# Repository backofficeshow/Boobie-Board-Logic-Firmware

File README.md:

# Boobie-Board-Logic-Firmware
Firmware For The Boobie Board Logic Analyser

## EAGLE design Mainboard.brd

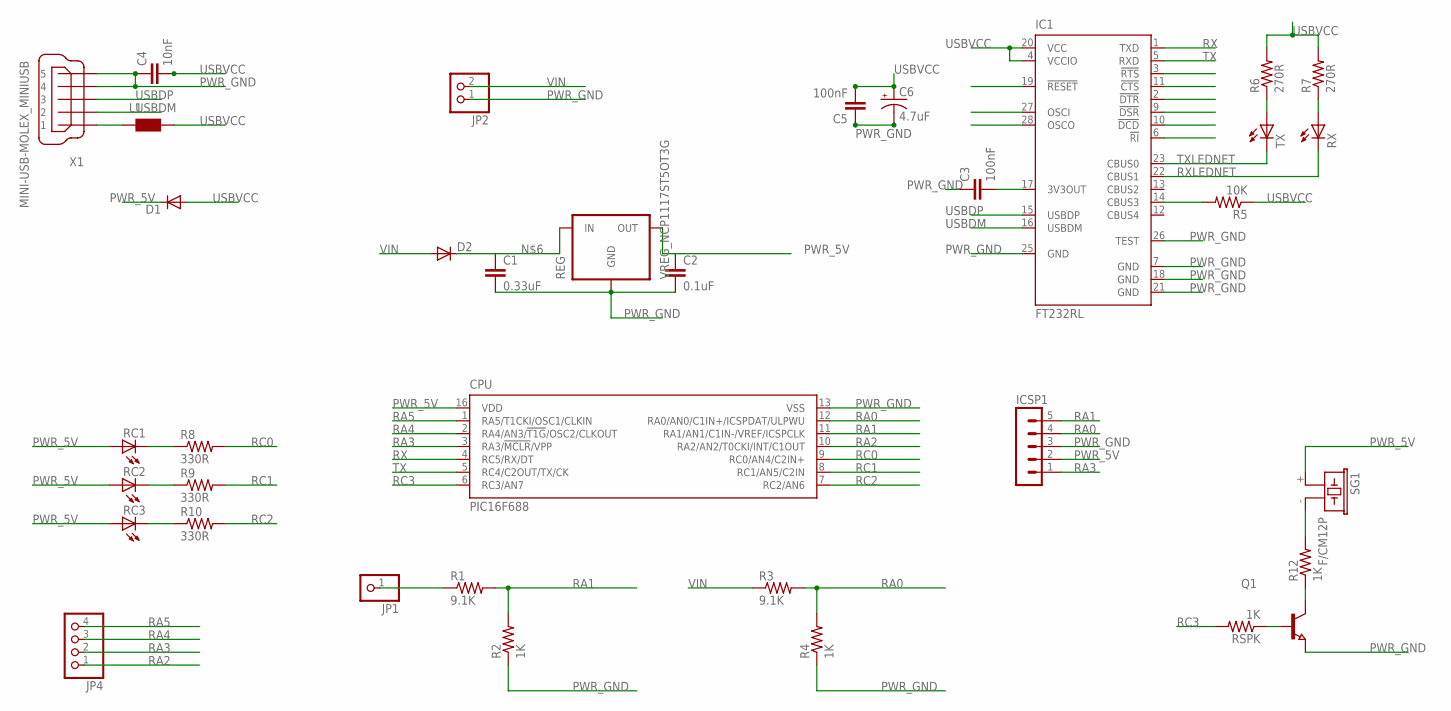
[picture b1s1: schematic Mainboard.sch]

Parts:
C1: 0.33uF; 0805
C2: 0.1uF; 0805
C3, C5: 100nF; 0805
C4: 10nF; 0805
C6: 4.7uF; EIA3528
CPU: PIC16F688; QFN16-4X4
D1, D2: DIODESMA; SMA-DIODE
IC1: FT232RL; SSOP28
ICSP1: MA05-1
JP1: PINHD-1X1; 1X01
JP2: PINHD-1X2; 1X02
JP4: PINHD-1X4; 1X04
L1: WE-CBF_0805; 0805
Q1: NPN-TRANSISTOR_SOT23; SOT23
R1, R3: 9.1K; 0805
R2, R4, R12: 1K; 0805
R5: 10K; 0805
R6, R7: 270R; 0805
R8, R9, R10: 330R; 0805
RC1, RC2, RC3: LED0603; LED-0603
REG: VREG_NCP1117ST5OT3G; SOT233
RSPK: 1K; 0805
RX: LED0603; LED-0603
SG1: F/CM12P
TX: LED0603; LED-0603
X1: MINI-USB-MOLEX_MINIUSB; 32005-201

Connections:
unnamed: R8.1, RC1.C
unnamed: JP1.1, R1.1
unnamed: R9.1, RC2.C
unnamed: R10.1, RC3.C
unnamed: R7.1, RX.A
unnamed: C1.1, D2.C, REG.3 (IN)
unnamed: C3.2, IC1.17 (3V3OUT)
unnamed: Q1.3 (C), R12.1
unnamed: Q1.1 (B), RSPK.1
unnamed: IC1.14 (CBUS3), R5.2
unnamed: L1.1, X1.1
unnamed: R12.2, SG1.- (2)
PWR_5V: C2.1, CPU.16 (VDD), D1.C, ICSP1.2, RC1.A, RC2.A, RC3.A, REG.2 (OUT), SG1.+ (1)
PWR_GND: C1.2, C2.2, C3.1, C4.1, C5.1, C6.C (-), CPU.13 (VSS), IC1.7 (GND), IC1.18 (GND), IC1.21 (GND), IC1.25 (GND), IC1.26 (TEST), ICSP1.3, JP2.1, Q1.2 (E), R2.1, R4.1, REG.1 (GND), X1.4, X1.5
RA0: CPU.12 (RA0/AN0/C1IN+/ICSPDAT/ULPWU), ICSP1.4, R3.2, R4.2
RA1: CPU.11 (RA1/AN1/C1IN-/VREF/ICSPCLK), ICSP1.5, R1.2, R2.2
RA2: CPU.10 (RA2/AN2/T0CKI/INT/C1OUT), JP4.1
RA3: CPU.3 (RA3/!MCLR!/VPP), ICSP1.1, JP4.2
RA4: CPU.2 (RA4/AN3/!T1G!/OSC2/CLKOUT), JP4.3
RA5: CPU.1 (RA5/T1CKI/OSC1/CLKIN), JP4.4
RC0: CPU.9 (RC0/AN4/C2IN+), R8.2
RC1: CPU.8 (RC1/AN5/C2IN), R9.2
RC2: CPU.7 (RC2/AN6), R10.2
RC3: CPU.6 (RC3/AN7), RSPK.2
RX: CPU.4 (RC5/RX/DT), IC1.1 (TXD)
RXLEDNET: IC1.22 (CBUS1), RX.C
TX: CPU.5 (RC4/C2OUT/TX/CK), IC1.5 (RXD)
TXLEDNET: IC1.23 (CBUS0), TX.C
TXNET: R6.1, TX.A
USBDM: IC1.16 (USBDM), X1.2
USBDP: IC1.15 (USBDP), X1.3
USBVCC: C4.2, C5.2, C6.A (+), D1.A, IC1.4 (VCCIO), IC1.20 (VCC), L1.2, R5.1, R6.2, R7.2
VIN: D2.A, JP2.2, R3.1

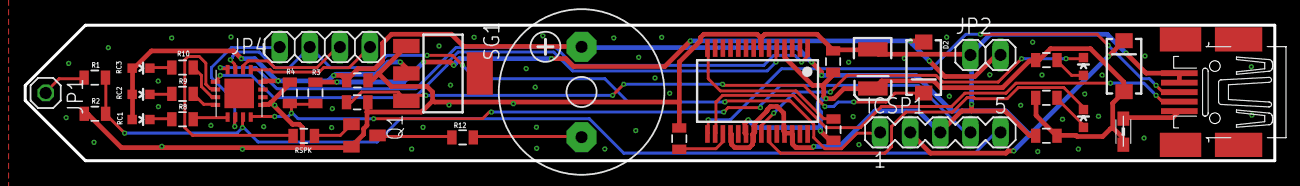
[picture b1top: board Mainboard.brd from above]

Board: 2 copper layers, 105.4 x 11.4 mm, 36 parts (0 on the bottom side), 33 nets.

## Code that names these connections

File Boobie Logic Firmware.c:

//ARCADE LOGIC
//Andrew Armstrong 18/04/2018
//www.backofficeshow.com

//Boobie Config = 
//Int OSC
//Ra0 (pin9) = Reference Voltage - use 1/100 voltage divider connected to VIN
//Ra1 (pin10) = Probe Voltage - use 1/10 voltage divider
//RC0 to RC2 (pin13 to 15) = Status LEDS
//POWERSRC JUMPER should be switched to VIN (not USB)

#include <16F688.h>
// C Optimised for the CCS PIC Compiler
// Using onboard clock
#fuses INTRC_IO,NOWDT,PUT, NOPROTECT,NOMCLR,NOFCMEN,BROWNOUT_SW//NOMCLR
#DEVICE ADC=10 //Give us the full 10 bits ADC!
#use delay(clock=8000000) //Not using the crystal
#use rs232(baud=57600, parity=N, xmit=PIN_C4, rcv=PIN_C5, bits=8, STOP=1)
#define version 1
#DEFINE LOW 0
#DEFINE HIGH 1
#DEFINE UNCERTAIN 3
#DEFINE OFF 255

#int_timer0
void timer0_isr(void)
{  

}

//Serial Interrupt
#INT_RDA
void SerialInt()
{
   getchar();
}

//Sets output based on status
void outputLEDs(unsigned char status)
{
   output_low(pin_c0);
   output_low(pin_c1);
   output_low(pin_c2);
   switch (status)
   {
      case OFF:
         break;
      case LOW:
         output_high(pin_c0);
         printf("L");
         break;
      case HIGH:
         output_high(pin_c2);
         printf("H");         
         break;      
      case UNCERTAIN:
         output_high(pin_c1);
         printf("U");
         break;      
   }
}

//Samples the ADC Port and returns a floating volt value
float read_analogue(unsigned char channel)
{
   float result = 0.0;
   int16 tempval = 0;
   char samples = 0;
   int16 average = 0.0;
   
   set_adc_channel(channel);
   for(samples = 1; samples <= 4; samples += 1)   
   {
      tempval = read_adc(); 
      average += tempval;               
      delay_us(10);   
   }
   
   average = average / 4;
   
   //Result_mV = ( Reference in mV / 1023) * Result
   //So for a reference of 3.3V (e.g.  using Vdd/Vss as ref) and ADC result of 250: 
   //Result = (3300/1023) * 250 = 806mV 
   
   result = average * (5000/1023); 

   result = result * 10;
   
   return result;                                 
   }

void main()
{
   float supplyVoltage; 
   float testVoltage;       
   
   setup_timer_0 ( RTCC_INTERNAL | RTCC_8_BIT | RTCC_DIV_2 );
   setup_adc(adc_clock_internal); //The ADC uses a clock to work
   setup_adc_ports(sAN0 | sAN1); //RC2 as analogue
   enable_interrupts(INT_RTCC);
   enable_interrupts(INT_RDA);
   enable_interrupts(GLOBAL);

   printf("\r\nBoobie Logic v%d\r\nAndrew Armstrong @backofficeshow\r\n", version);

   outputLEDs(OFF);

   while (TRUE)
   {
      supplyVoltage = read_analogue(0); 
      testVoltage = read_analogue(1); 
      
      printf("%02.2fv ", testVoltage / 1000);
      
      if ((supplyVoltage >= 4700) && (supplyVoltage <= 5250)) //TTL Logic
      {
         printf("T ");
         if (testVoltage >= 2000)
         {
            outputLEDs(HIGH);
         }
         else if (testVoltage <= 800)
         {
            outputLEDs(LOW);
         }
         else
         {
            outputLEDs(UNCERTAIN);
         }
      }
      else //CMOS Logic
      {
         printf("C ");
         if (testVoltage >= supplyVoltage*0.66)
         {
            outputLEDs(HIGH);
         }
         else if (testVoltage <= supplyVoltage*0.33)
         {
            outputLEDs(LOW);
         }
         else
         {
            outputLEDs(UNCERTAIN);
         }
      }
      printf("\r\n");
   }  
} 

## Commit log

2018-04-19 Updated error in description
2018-04-19 Eagle CAD files for v1.0 ALPHA
